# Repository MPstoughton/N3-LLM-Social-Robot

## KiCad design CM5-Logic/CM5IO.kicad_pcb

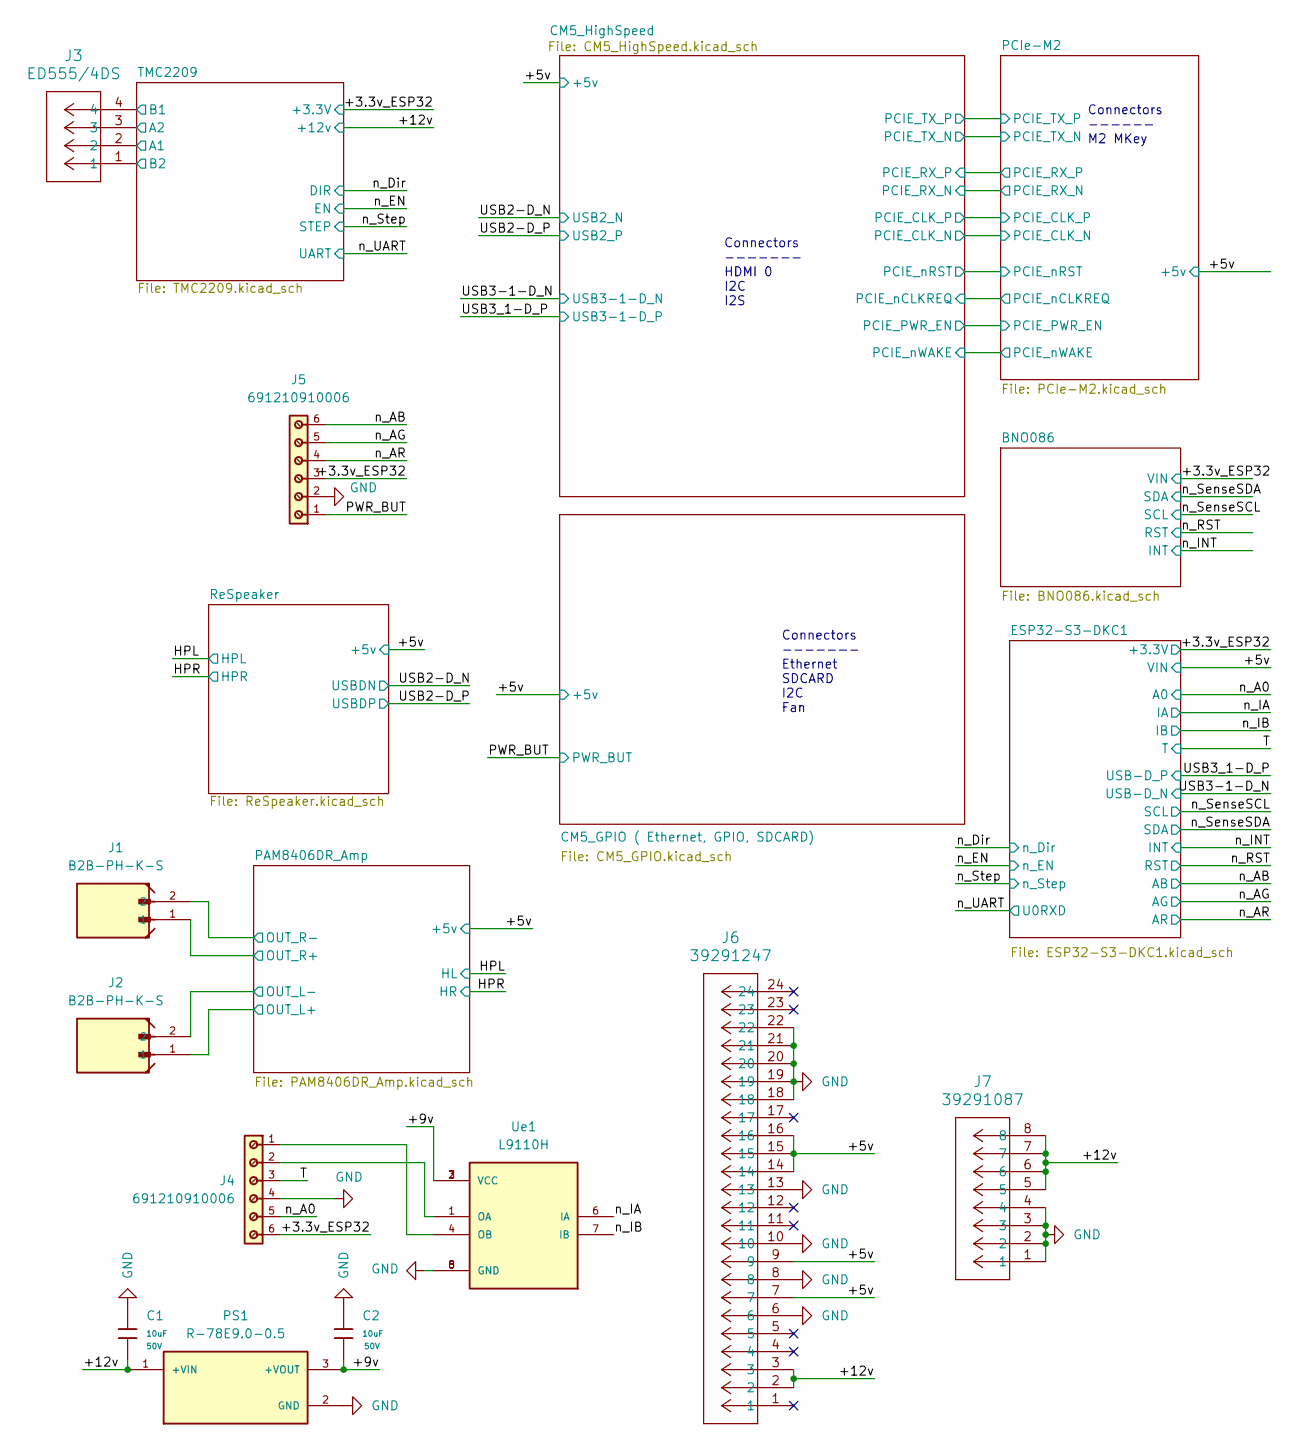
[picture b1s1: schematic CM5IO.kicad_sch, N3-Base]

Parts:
C1, C2: 10uF; C_1206; Voltage Rated 50V; Tolerance ±10%; Part CL31A106KBHNNNE; LCSC C13585
J1, J2: B2B-PH-K-S; JST_B2B-PH-K-S
J3: ED555/4DS; CONN4_ED555&slash_4DS_SHT
J4, J5: 691210910006
J6: 39291247; CONN_SD-5569-002_24_MOL
J7: 39291087; CONN_SD-5569-002_08_MOL
PS1: R-78E9.0-0.5; CONV_R-78E9.0-0.5; PARTREV 4
Ue1: L9110H; SOIC127P599X172-8N; PARTREV NA

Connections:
/+3.3v_ESP32: J4.6, J5.3; also elsewhere on the board
/+5v: J6.7, J6.9, J6.14, J6.15, J6.16; also elsewhere on the board
/+9v: C2.1, PS1.3 (+VOUT), Ue1.2 (VCC), Ue1.3 (VCC)
/+12v: C1.1, J6.2, J6.3, J7.5, J7.6, J7.7, J7.8, PS1.1 (+VIN); also elsewhere on the board
/PAM8406DR_Amp/OUT_L+: J2.1; also elsewhere on the board
/PAM8406DR_Amp/OUT_L-: J2.2; also elsewhere on the board
/PAM8406DR_Amp/OUT_R+: J1.1; also elsewhere on the board
/PAM8406DR_Amp/OUT_R-: J1.2; also elsewhere on the board
/PWR_BUT: J5.1; also elsewhere on the board
/T: J4.3; also elsewhere on the board
/TMC2209/A1: J3.2; also elsewhere on the board
/TMC2209/A2: J3.3; also elsewhere on the board
/TMC2209/B1: J3.4; also elsewhere on the board
/TMC2209/B2: J3.1; also elsewhere on the board
/n_A0: J4.5; also elsewhere on the board
/n_AB: J5.6; also elsewhere on the board
/n_AG: J5.5; also elsewhere on the board
/n_AR: J5.4; also elsewhere on the board
/n_IA: Ue1.6 (IA); also elsewhere on the board
/n_IB: Ue1.7 (IB); also elsewhere on the board
GND: C1.2, C2.2, J4.4, J5.2, J6.6, J6.8, J6.10, J6.13, J6.18, J6.19, J6.20, J6.21, J6.22, J7.1, J7.2, J7.3, J7.4, PS1.2 (GND), Ue1.5 (GND), Ue1.8 (GND); also elsewhere on the board
unnamed: J4.2, Ue1.1 (OA)
unnamed: J4.1, Ue1.4 (OB)

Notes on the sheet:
Connectors ------- Ethernet SDCARD I2C Fan
Connectors ------ M2 MKey
Connectors ------- HDMI 0 I2C I2S

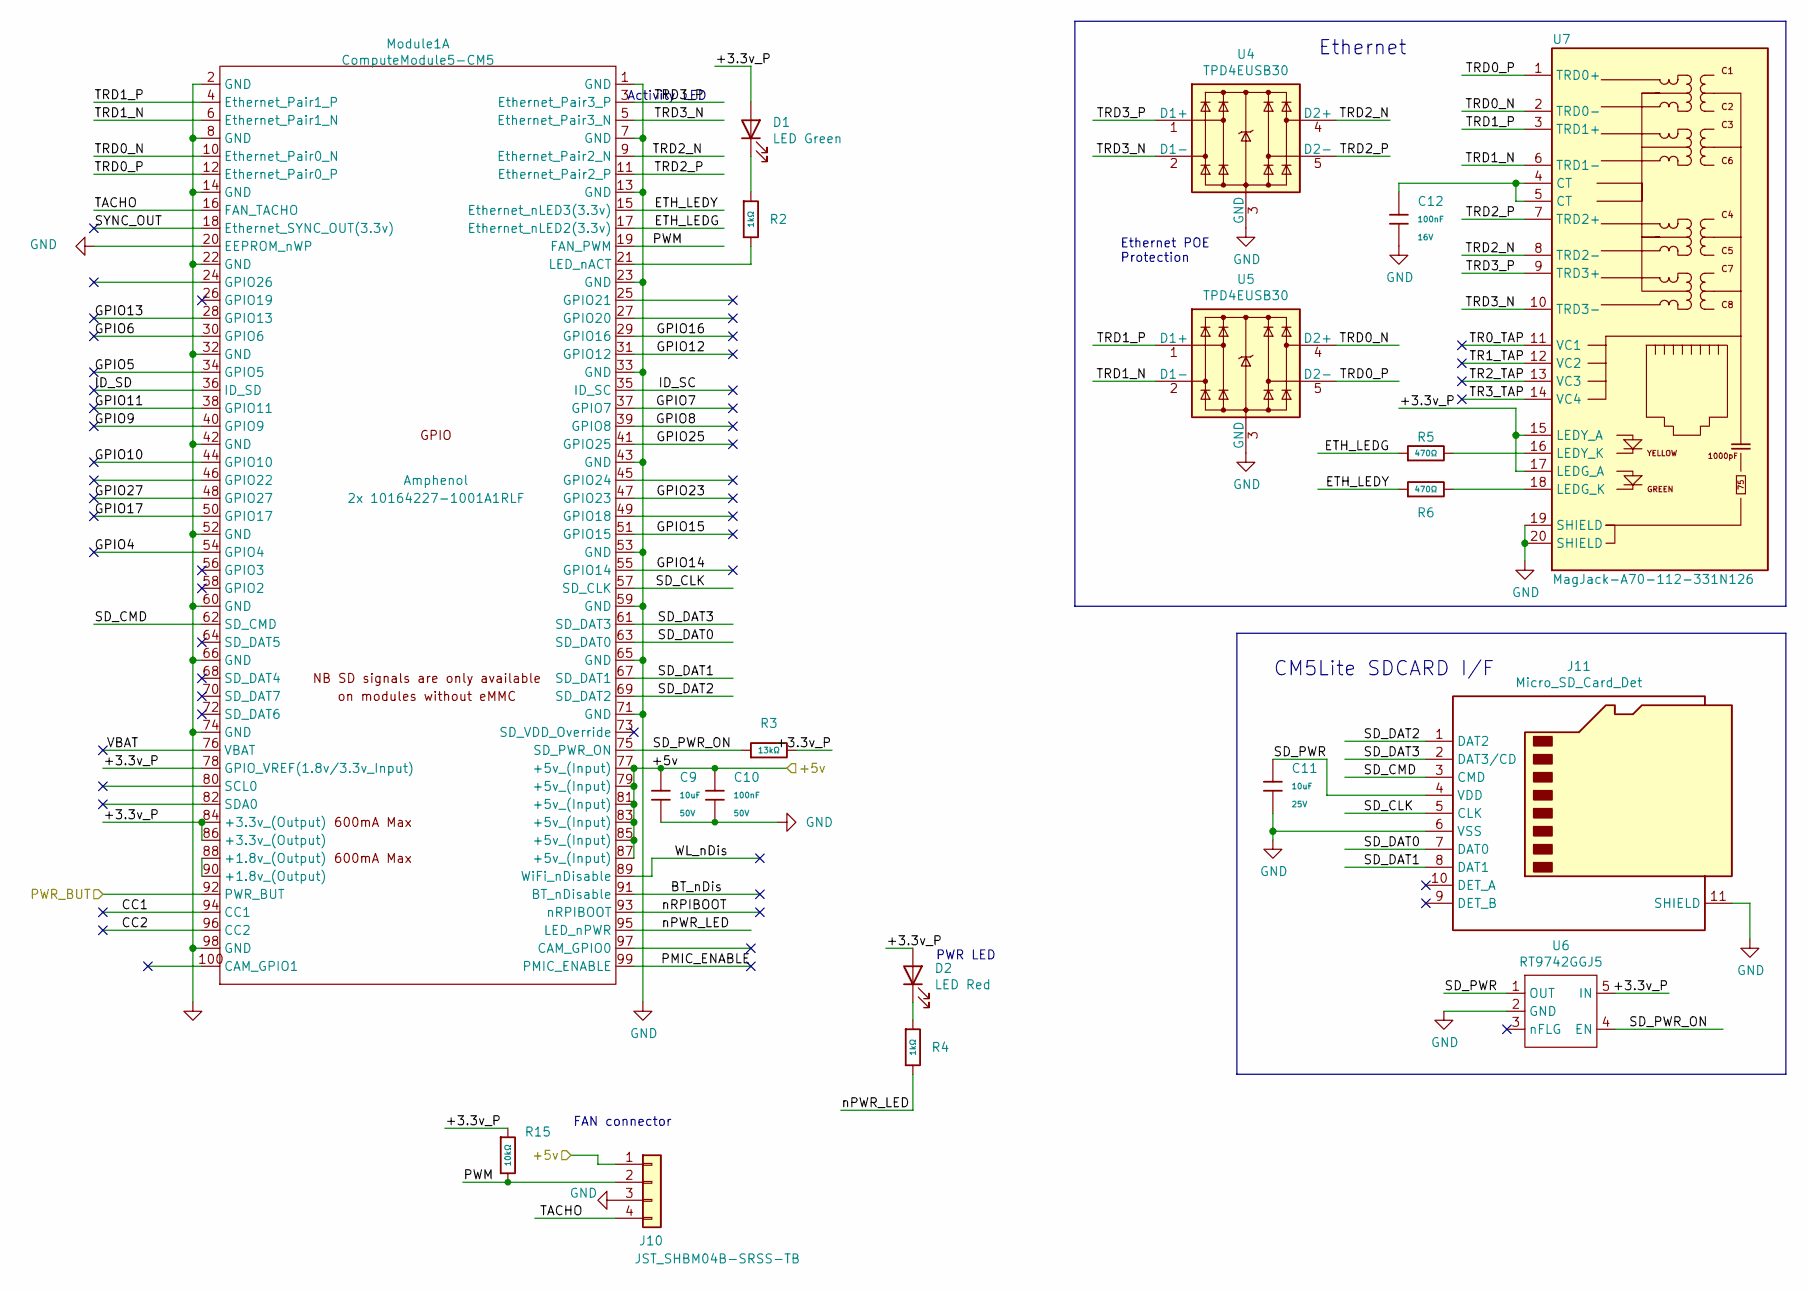
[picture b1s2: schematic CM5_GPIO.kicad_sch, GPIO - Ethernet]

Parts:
C9: 10uF; C_1206; Voltage Rated 50V; Tolerance ±10%; Part CL31A106KBHNNNE; LCSC C13585
C10: 100nF; C_0603; Voltage Rated 50V; Tolerance ±10%; Part CC0603KRX7R9BB104; LCSC C14663
C11: 10uF; C_0805; Voltage Rated 25V; Tolerance ±10%; Part CL21A106KAYNNNE; LCSC C15850
C12: 100nF; C_0402; Voltage Rated 16V; Tolerance ±10%; Part CL05B104KO5NNNC; LCSC C1525
D1: LED Green; LED_0603_1608Metric; Part Description Green 572nm LED Indication - Discrete 2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
D2: LED Red; LED_0603_1608Metric; Part Description Red 620nm LED Indication - Discrete 2.2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
J10: JST_SHBM04B-SRSS-TB; JST_SH_BM04B-SRSS-TB_1x04-1MP_P1.00mm_Vertical; Part Description 4 pin vertical 1mm pitch connector
J11: Micro_SD_Card_Det; SDCARD_MOLEX_503398-1892; Part Description 9 (8 + 1) Position Card Connector micro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
Module1: ComputeModule5-CM5; Raspberry-Pi-5-Compute-Module; Part Description 100 Position Connector Receptacle, Cent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
R2, R4: 1kΩ; R_0402; Overload Voltage (Max) 50V; Tolerance ±1%; Part 0402WGF1001TCE; LCSC C11702
R3: 13kΩ; R_0805; Overload Voltage (Max) 150V; Tolerance ±1%; Part 0805W8F1302T5E; LCSC C17455
R5, R6: 470Ω; R_0402; Overload Voltage (Max) 50V; Tolerance ±1%; Part 0402WGF4700TCE; LCSC C25117
R15: 10kΩ; R_0402; Overload Voltage (Max) 50V; Tolerance ±1%; Part 0402WGF1002TCE; LCSC C25744
U4, U5: TPD4EUSB30; USON-10_2.5x1.0mm_P0.5mm; Part Description Quad TVS diode for high speed signals (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
U6: RT9742GGJ5; SOT-23-5; Part Description Power Switch/Driver 1:1 N-Channel 1A TS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
U7: MagJack-A70-112-331N126; TRJG0926HENL; Part Description Gigabit Ethernet Magjack

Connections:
/+5v: C9.1, C10.1, J10.1, Module1.77 (+5v_(Input)), Module1.79 (+5v_(Input)), Module1.81 (+5v_(Input)), Module1.83 (+5v_(Input)), Module1.85 (+5v_(Input)), Module1.87 (+5v_(Input)); also elsewhere on the board
/CM5_GPIO ( Ethernet, GPIO, SDCARD)/+3.3v_P: D1.2 (A), D2.2 (A), Module1.78 (GPIO_VREF(1.8v/3.3v_Input)), Module1.84 (+3.3v_(Output)), Module1.86 (+3.3v_(Output)), R3.2, R15.1, U6.5 (IN), U7.15 (LEDY_A), U7.17 (LEDG_A)
/CM5_GPIO ( Ethernet, GPIO, SDCARD)/BT_nDis: Module1.91 (BT_nDisable)
/CM5_GPIO ( Ethernet, GPIO, SDCARD)/CC1: Module1.94 (CC1)
/CM5_GPIO ( Ethernet, GPIO, SDCARD)/CC2: Module1.96 (CC2)
/CM5_GPIO ( Ethernet, GPIO, SDCARD)/ETH_LEDG: Module1.17 (Ethernet_nLED2(3.3v)), R5.1
/CM5_GPIO ( Ethernet, GPIO, SDCARD)/ETH_LEDY: Module1.15 (Ethernet_nLED3(3.3v)), R6.1
/CM5_GPIO ( Ethernet, GPIO, SDCARD)/GPIO4: Module1.54 (GPIO4)
/CM5_GPIO ( Ethernet, GPIO, SDCARD)/GPIO5: Module1.34 (GPIO5)
/CM5_GPIO ( Ethernet, GPIO, SDCARD)/GPIO6: Module1.30 (GPIO6)
/CM5_GPIO ( Ethernet, GPIO, SDCARD)/GPIO7: Module1.37 (GPIO7)
/CM5_GPIO ( Ethernet, GPIO, SDCARD)/GPIO8: Module1.39 (GPIO8)
/CM5_GPIO ( Ethernet, GPIO, SDCARD)/GPIO9: Module1.40 (GPIO9)
/CM5_GPIO ( Ethernet, GPIO, SDCARD)/GPIO10: Module1.44 (GPIO10)
/CM5_GPIO ( Ethernet, GPIO, SDCARD)/GPIO11: Module1.38 (GPIO11)
/CM5_GPIO ( Ethernet, GPIO, SDCARD)/GPIO12: Module1.31 (GPIO12)
/CM5_GPIO ( Ethernet, GPIO, SDCARD)/GPIO13: Module1.28 (GPIO13)
/CM5_GPIO ( Ethernet, GPIO, SDCARD)/GPIO14: Module1.55 (GPIO14)
/CM5_GPIO ( Ethernet, GPIO, SDCARD)/GPIO15: Module1.51 (GPIO15)
/CM5_GPIO ( Ethernet, GPIO, SDCARD)/GPIO16: Module1.29 (GPIO16)
/CM5_GPIO ( Ethernet, GPIO, SDCARD)/GPIO17: Module1.50 (GPIO17)
/CM5_GPIO ( Ethernet, GPIO, SDCARD)/GPIO23: Module1.47 (GPIO23)
/CM5_GPIO ( Ethernet, GPIO, SDCARD)/GPIO25: Module1.41 (GPIO25)
/CM5_GPIO ( Ethernet, GPIO, SDCARD)/GPIO27: Module1.48 (GPIO27)
/CM5_GPIO ( Ethernet, GPIO, SDCARD)/ID_SC: Module1.35 (ID_SC)
/CM5_GPIO ( Ethernet, GPIO, SDCARD)/ID_SD: Module1.36 (ID_SD)
/CM5_GPIO ( Ethernet, GPIO, SDCARD)/PMIC_ENABLE: Module1.99 (PMIC_ENABLE)
/CM5_GPIO ( Ethernet, GPIO, SDCARD)/PWM: J10.2, Module1.19 (FAN_PWM), R15.2
/CM5_GPIO ( Ethernet, GPIO, SDCARD)/SD_CLK: J11.5 (CLK), Module1.57 (SD_CLK)
/CM5_GPIO ( Ethernet, GPIO, SDCARD)/SD_CMD: J11.3 (CMD), Module1.62 (SD_CMD)
/CM5_GPIO ( Ethernet, GPIO, SDCARD)/SD_DAT0: J11.7 (DAT0), Module1.63 (SD_DAT0)
/CM5_GPIO ( Ethernet, GPIO, SDCARD)/SD_DAT1: J11.8 (DAT1), Module1.67 (SD_DAT1)
/CM5_GPIO ( Ethernet, GPIO, SDCARD)/SD_DAT2: J11.1 (DAT2), Module1.69 (SD_DAT2)
/CM5_GPIO ( Ethernet, GPIO, SDCARD)/SD_DAT3: J11.2 (DAT3/CD), Module1.61 (SD_DAT3)
/CM5_GPIO ( Ethernet, GPIO, SDCARD)/SD_PWR: C11.1, J11.4 (VDD), U6.1 (OUT)
/CM5_GPIO ( Ethernet, GPIO, SDCARD)/SD_PWR_ON: Module1.75 (SD_PWR_ON), R3.1, U6.4 (EN)
/CM5_GPIO ( Ethernet, GPIO, SDCARD)/SYNC_OUT: Module1.18 (Ethernet_SYNC_OUT(3.3v))
/CM5_GPIO ( Ethernet, GPIO, SDCARD)/TACHO: J10.4, Module1.16 (FAN_TACHO)
/CM5_GPIO ( Ethernet, GPIO, SDCARD)/TR0_TAP: U7.11 (VC1)
/CM5_GPIO ( Ethernet, GPIO, SDCARD)/TR1_TAP: U7.12 (VC2)
/CM5_GPIO ( Ethernet, GPIO, SDCARD)/TR2_TAP: U7.13 (VC3)
/CM5_GPIO ( Ethernet, GPIO, SDCARD)/TR3_TAP: U7.14 (VC4)
/CM5_GPIO ( Ethernet, GPIO, SDCARD)/TRD0_N: Module1.10 (Ethernet_Pair0_N), U5.4 (D2+), U5.7, U7.2 (TRD0-)
/CM5_GPIO ( Ethernet, GPIO, SDCARD)/TRD0_P: Module1.12 (Ethernet_Pair0_P), U5.5 (D2-), U5.6, U7.1 (TRD0+)
/CM5_GPIO ( Ethernet, GPIO, SDCARD)/TRD1_N: Module1.6 (Ethernet_Pair1_N), U5.2 (D1-), U5.9, U7.6 (TRD1-)
/CM5_GPIO ( Ethernet, GPIO, SDCARD)/TRD1_P: Module1.4 (Ethernet_Pair1_P), U5.1 (D1+), U5.10, U7.3 (TRD1+)
/CM5_GPIO ( Ethernet, GPIO, SDCARD)/TRD2_N: Module1.9 (Ethernet_Pair2_N), U4.4 (D2+), U4.7, U7.8 (TRD2-)
/CM5_GPIO ( Ethernet, GPIO, SDCARD)/TRD2_P: Module1.11 (Ethernet_Pair2_P), U4.5 (D2-), U4.6, U7.7 (TRD2+)
/CM5_GPIO ( Ethernet, GPIO, SDCARD)/TRD3_N: Module1.5 (Ethernet_Pair3_N), U4.2 (D1-), U4.9, U7.10 (TRD3-)
/CM5_GPIO ( Ethernet, GPIO, SDCARD)/TRD3_P: Module1.3 (Ethernet_Pair3_P), U4.1 (D1+), U4.10, U7.9 (TRD3+)
/CM5_GPIO ( Ethernet, GPIO, SDCARD)/VBAT: Module1.76 (VBAT)
/CM5_GPIO ( Ethernet, GPIO, SDCARD)/WL_nDis: Module1.89 (WiFi_nDisable)
/CM5_GPIO ( Ethernet, GPIO, SDCARD)/nPWR_LED: Module1.95 (LED_nPWR), R4.2
/CM5_GPIO ( Ethernet, GPIO, SDCARD)/nRPIBOOT: Module1.93 (nRPIBOOT)
/PWR_BUT: Module1.92 (PWR_BUT); also elsewhere on the board
GND: C9.2, C10.2, C11.2, C12.2, J10.3, J11.6 (VSS), J11.11 (SHIELD), Module1.1 (GND), Module1.2 (GND), Module1.7 (GND), Module1.8 (GND), Module1.13 (GND), Module1.14 (GND), Module1.20 (EEPROM_nWP), Module1.22 (GND), Module1.23 (GND), Module1.32 (GND), Module1.33 (GND), Module1.42 (GND), Module1.43 (GND), Module1.52 (GND), Module1.53 (GND), Module1.59 (GND), Module1.60 (GND), Module1.65 (GND), Module1.66 (GND), Module1.71 (GND), Module1.74 (GND), Module1.98 (GND), U4.3 (GND), U4.8 (GND), U5.3 (GND), U5.8 (GND), U6.2 (GND), U7.19 (SHIELD), U7.20 (SHIELD); also elsewhere on the board
unnamed: C12.1, U7.4 (CT), U7.5 (CT)
unnamed: D1.1 (K), R2.1
unnamed: D2.1 (K), R4.1
unnamed: Module1.88 (+1.8v_(Output)), Module1.90 (+1.8v_(Output))
unnamed: Module1.21 (LED_nACT), R2.2
unnamed: R6.2, U7.18 (LEDG_K)
unnamed: R5.2, U7.16 (LEDY_K)

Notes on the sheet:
Activity LED
FAN connector
Ethernet POE Protection
PWR LED
Ethernet
CM5Lite SDCARD I/F

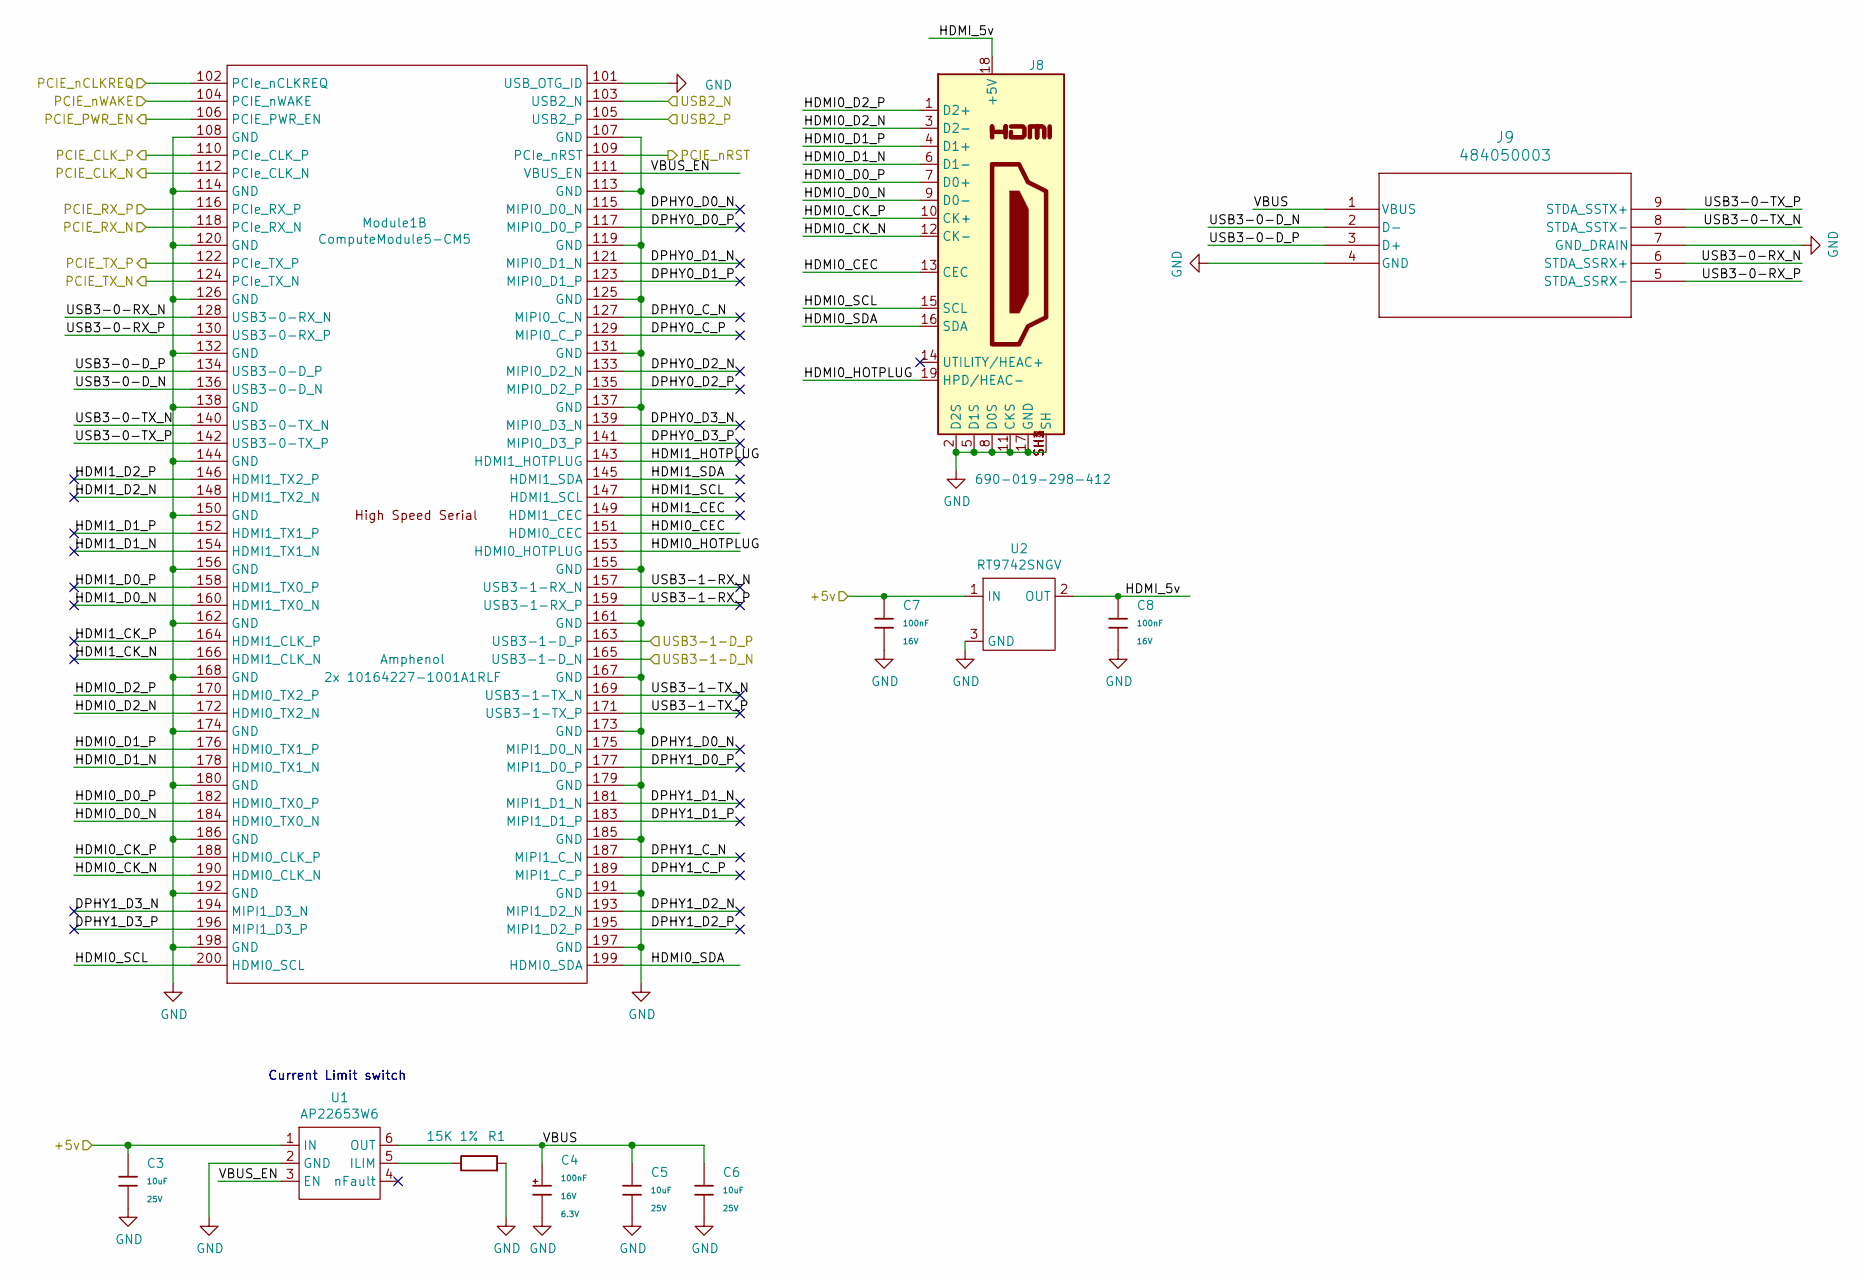
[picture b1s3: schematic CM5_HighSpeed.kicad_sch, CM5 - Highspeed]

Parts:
C3, C5, C6: 10uF; C_0805; Voltage Rated 25V; Tolerance ±10%; Part CL21A106KAYNNNE; LCSC C15850
C4: 100nF; C_CASE-B-3528-21(mm); Voltage Rated 16V; Tolerance ±10%; Part TAJB107K006RNJ; LCSC C16133
C7, C8: 100nF; C_0402; Voltage Rated 16V; Tolerance ±10%; Part CL05B104KO5NNNC; LCSC C1525
J8: 690-019-298-412; EDAC 690-019-298-412; Part Description HDMI Connector, Right Angle, 19 Contact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
J9: 484050003; 484050003_MOL
Module1: ComputeModule5-CM5; Raspberry-Pi-5-Compute-Module; Part Description 100 Position Connector Receptacle, Cent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
R1: 15K 1%; R_0402_1005Metric; Part Description Resistor 15K M1005 1% 63mW
U1: AP22653W6; SOT-23-6; Part Description Power Switch/Driver 1:1 P-Channel 2.1A 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
U2: RT9742SNGV; TSOT-23_HandSoldering; Part Description Power Switch/Driver 1:1 N-Channel 500mA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

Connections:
/+5v: C3.1, C7.1, U1.1 (IN), U2.1 (IN); also elsewhere on the board
/CM5_HighSpeed/DPHY0_C_N: Module1.127 (MIPI0_C_N)
/CM5_HighSpeed/DPHY0_C_P: Module1.129 (MIPI0_C_P)
/CM5_HighSpeed/DPHY0_D0_N: Module1.115 (MIPI0_D0_N)
/CM5_HighSpeed/DPHY0_D0_P: Module1.117 (MIPI0_D0_P)
/CM5_HighSpeed/DPHY0_D1_N: Module1.121 (MIPI0_D1_N)
/CM5_HighSpeed/DPHY0_D1_P: Module1.123 (MIPI0_D1_P)
/CM5_HighSpeed/DPHY0_D2_N: Module1.133 (MIPI0_D2_N)
/CM5_HighSpeed/DPHY0_D2_P: Module1.135 (MIPI0_D2_P)
/CM5_HighSpeed/DPHY0_D3_N: Module1.139 (MIPI0_D3_N)
/CM5_HighSpeed/DPHY0_D3_P: Module1.141 (MIPI0_D3_P)
/CM5_HighSpeed/DPHY1_C_N: Module1.187 (MIPI1_C_N)
/CM5_HighSpeed/DPHY1_C_P: Module1.189 (MIPI1_C_P)
/CM5_HighSpeed/DPHY1_D0_N: Module1.175 (MIPI1_D0_N)
/CM5_HighSpeed/DPHY1_D0_P: Module1.177 (MIPI1_D0_P)
/CM5_HighSpeed/DPHY1_D1_N: Module1.181 (MIPI1_D1_N)
/CM5_HighSpeed/DPHY1_D1_P: Module1.183 (MIPI1_D1_P)
/CM5_HighSpeed/DPHY1_D2_N: Module1.193 (MIPI1_D2_N)
/CM5_HighSpeed/DPHY1_D2_P: Module1.195 (MIPI1_D2_P)
/CM5_HighSpeed/DPHY1_D3_N: Module1.194 (MIPI1_D3_N)
/CM5_HighSpeed/DPHY1_D3_P: Module1.196 (MIPI1_D3_P)
/CM5_HighSpeed/HDMI0_CEC: J8.13 (CEC), Module1.151 (HDMI0_CEC)
/CM5_HighSpeed/HDMI0_CK_N: J8.12 (CK-), Module1.190 (HDMI0_CLK_N)
/CM5_HighSpeed/HDMI0_CK_P: J8.10 (CK+), Module1.188 (HDMI0_CLK_P)
/CM5_HighSpeed/HDMI0_D0_N: J8.9 (D0-), Module1.184 (HDMI0_TX0_N)
/CM5_HighSpeed/HDMI0_D0_P: J8.7 (D0+), Module1.182 (HDMI0_TX0_P)
/CM5_HighSpeed/HDMI0_D1_N: J8.6 (D1-), Module1.178 (HDMI0_TX1_N)
/CM5_HighSpeed/HDMI0_D1_P: J8.4 (D1+), Module1.176 (HDMI0_TX1_P)
/CM5_HighSpeed/HDMI0_D2_N: J8.3 (D2-), Module1.172 (HDMI0_TX2_N)
/CM5_HighSpeed/HDMI0_D2_P: J8.1 (D2+), Module1.170 (HDMI0_TX2_P)
/CM5_HighSpeed/HDMI0_HOTPLUG: J8.19 (HPD/HEAC-), Module1.153 (HDMI0_HOTPLUG)
/CM5_HighSpeed/HDMI0_SCL: J8.15 (SCL), Module1.200 (HDMI0_SCL)
/CM5_HighSpeed/HDMI0_SDA: J8.16 (SDA), Module1.199 (HDMI0_SDA)
/CM5_HighSpeed/HDMI1_CEC: Module1.149 (HDMI1_CEC)
/CM5_HighSpeed/HDMI1_CK_N: Module1.166 (HDMI1_CLK_N)
/CM5_HighSpeed/HDMI1_CK_P: Module1.164 (HDMI1_CLK_P)
/CM5_HighSpeed/HDMI1_D0_N: Module1.160 (HDMI1_TX0_N)
/CM5_HighSpeed/HDMI1_D0_P: Module1.158 (HDMI1_TX0_P)
/CM5_HighSpeed/HDMI1_D1_N: Module1.154 (HDMI1_TX1_N)
/CM5_HighSpeed/HDMI1_D1_P: Module1.152 (HDMI1_TX1_P)
/CM5_HighSpeed/HDMI1_D2_N: Module1.148 (HDMI1_TX2_N)
/CM5_HighSpeed/HDMI1_D2_P: Module1.146 (HDMI1_TX2_P)
/CM5_HighSpeed/HDMI1_HOTPLUG: Module1.143 (HDMI1_HOTPLUG)
/CM5_HighSpeed/HDMI1_SCL: Module1.147 (HDMI1_SCL)
/CM5_HighSpeed/HDMI1_SDA: Module1.145 (HDMI1_SDA)
/CM5_HighSpeed/HDMI_5v: C8.1, J8.18 (+5V), U2.2 (OUT)
/CM5_HighSpeed/PCIE_CLK_N: Module1.112 (PCIe_CLK_N); also elsewhere on the board
/CM5_HighSpeed/PCIE_CLK_P: Module1.110 (PCIe_CLK_P); also elsewhere on the board
/CM5_HighSpeed/PCIE_PWR_EN: Module1.106 (PCIE_PWR_EN); also elsewhere on the board
/CM5_HighSpeed/PCIE_RX_N: Module1.118 (PCIe_RX_N); also elsewhere on the board
/CM5_HighSpeed/PCIE_RX_P: Module1.116 (PCIe_RX_P); also elsewhere on the board
/CM5_HighSpeed/PCIE_TX_N: Module1.124 (PCIe_TX_N); also elsewhere on the board
/CM5_HighSpeed/PCIE_TX_P: Module1.122 (PCIe_TX_P); also elsewhere on the board
/CM5_HighSpeed/PCIE_nCLKREQ: Module1.102 (PCIe_nCLKREQ); also elsewhere on the board
/CM5_HighSpeed/PCIE_nRST: Module1.109 (PCIe_nRST); also elsewhere on the board
/CM5_HighSpeed/PCIE_nWAKE: Module1.104 (PCIE_nWAKE); also elsewhere on the board
/CM5_HighSpeed/USB3-0-D_N: J9.2 (D-), Module1.136 (USB3-0-D_N)
/CM5_HighSpeed/USB3-0-D_P: J9.3 (D+), Module1.134 (USB3-0-D_P)
/CM5_HighSpeed/USB3-0-RX_N: J9.6 (STDA_SSRX+), Module1.128 (USB3-0-RX_N)
/CM5_HighSpeed/USB3-0-RX_P: J9.5 (STDA_SSRX-), Module1.130 (USB3-0-RX_P)
/CM5_HighSpeed/USB3-0-TX_N: J9.8 (STDA_SSTX-), Module1.140 (USB3-0-TX_N)
/CM5_HighSpeed/USB3-0-TX_P: J9.9 (STDA_SSTX+), Module1.142 (USB3-0-TX_P)
/CM5_HighSpeed/USB3-1-RX_N: Module1.157 (USB3-1-RX_N)
/CM5_HighSpeed/USB3-1-RX_P: Module1.159 (USB3-1-RX_P)
/CM5_HighSpeed/USB3-1-TX_N: Module1.169 (USB3-1-TX_N)
/CM5_HighSpeed/USB3-1-TX_P: Module1.171 (USB3-1-TX_P)
/CM5_HighSpeed/VBUS: C4.1, C5.1, C6.1, J9.1 (VBUS), U1.6 (OUT)
/CM5_HighSpeed/VBUS_EN: Module1.111 (VBUS_EN), U1.3 (EN)
/USB2-D_N: Module1.103 (USB2_N); also elsewhere on the board
/USB2-D_P: Module1.105 (USB2_P); also elsewhere on the board
/USB3-1-D_N: Module1.165 (USB3-1-D_N); also elsewhere on the board
/USB3_1-D_P: Module1.163 (USB3-1-D_P); also elsewhere on the board
GND: C3.2, C4.2, C5.2, C6.2, C7.2, C8.2, J8.2 (D2S), J8.5 (D1S), J8.8 (D0S), J8.11 (CKS), J8.17 (GND), J8.SH1 (SH), J8.SH2 (SH), J8.SH3 (SH), J8.SH4 (SH), J9.4 (GND), J9.7 (GND_DRAIN), Module1.101 (USB_OTG_ID), Module1.107 (GND), Module1.108 (GND), Module1.113 (GND), Module1.114 (GND), Module1.119 (GND), Module1.120 (GND), Module1.125 (GND), Module1.126 (GND), Module1.131 (GND), Module1.132 (GND), Module1.137 (GND), Module1.138 (GND), Module1.144 (GND), Module1.150 (GND), Module1.155 (GND), Module1.156 (GND), Module1.161 (GND), Module1.162 (GND), Module1.167 (GND), Module1.168 (GND), Module1.173 (GND), Module1.174 (GND), Module1.179 (GND), Module1.180 (GND), Module1.185 (GND), Module1.186 (GND), Module1.191 (GND), Module1.192 (GND), Module1.197 (GND), Module1.198 (GND), R1.2, U1.2 (GND), U2.3 (GND); also elsewhere on the board
unnamed: R1.1, U1.5 (ILIM)

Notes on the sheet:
Current Limit switch

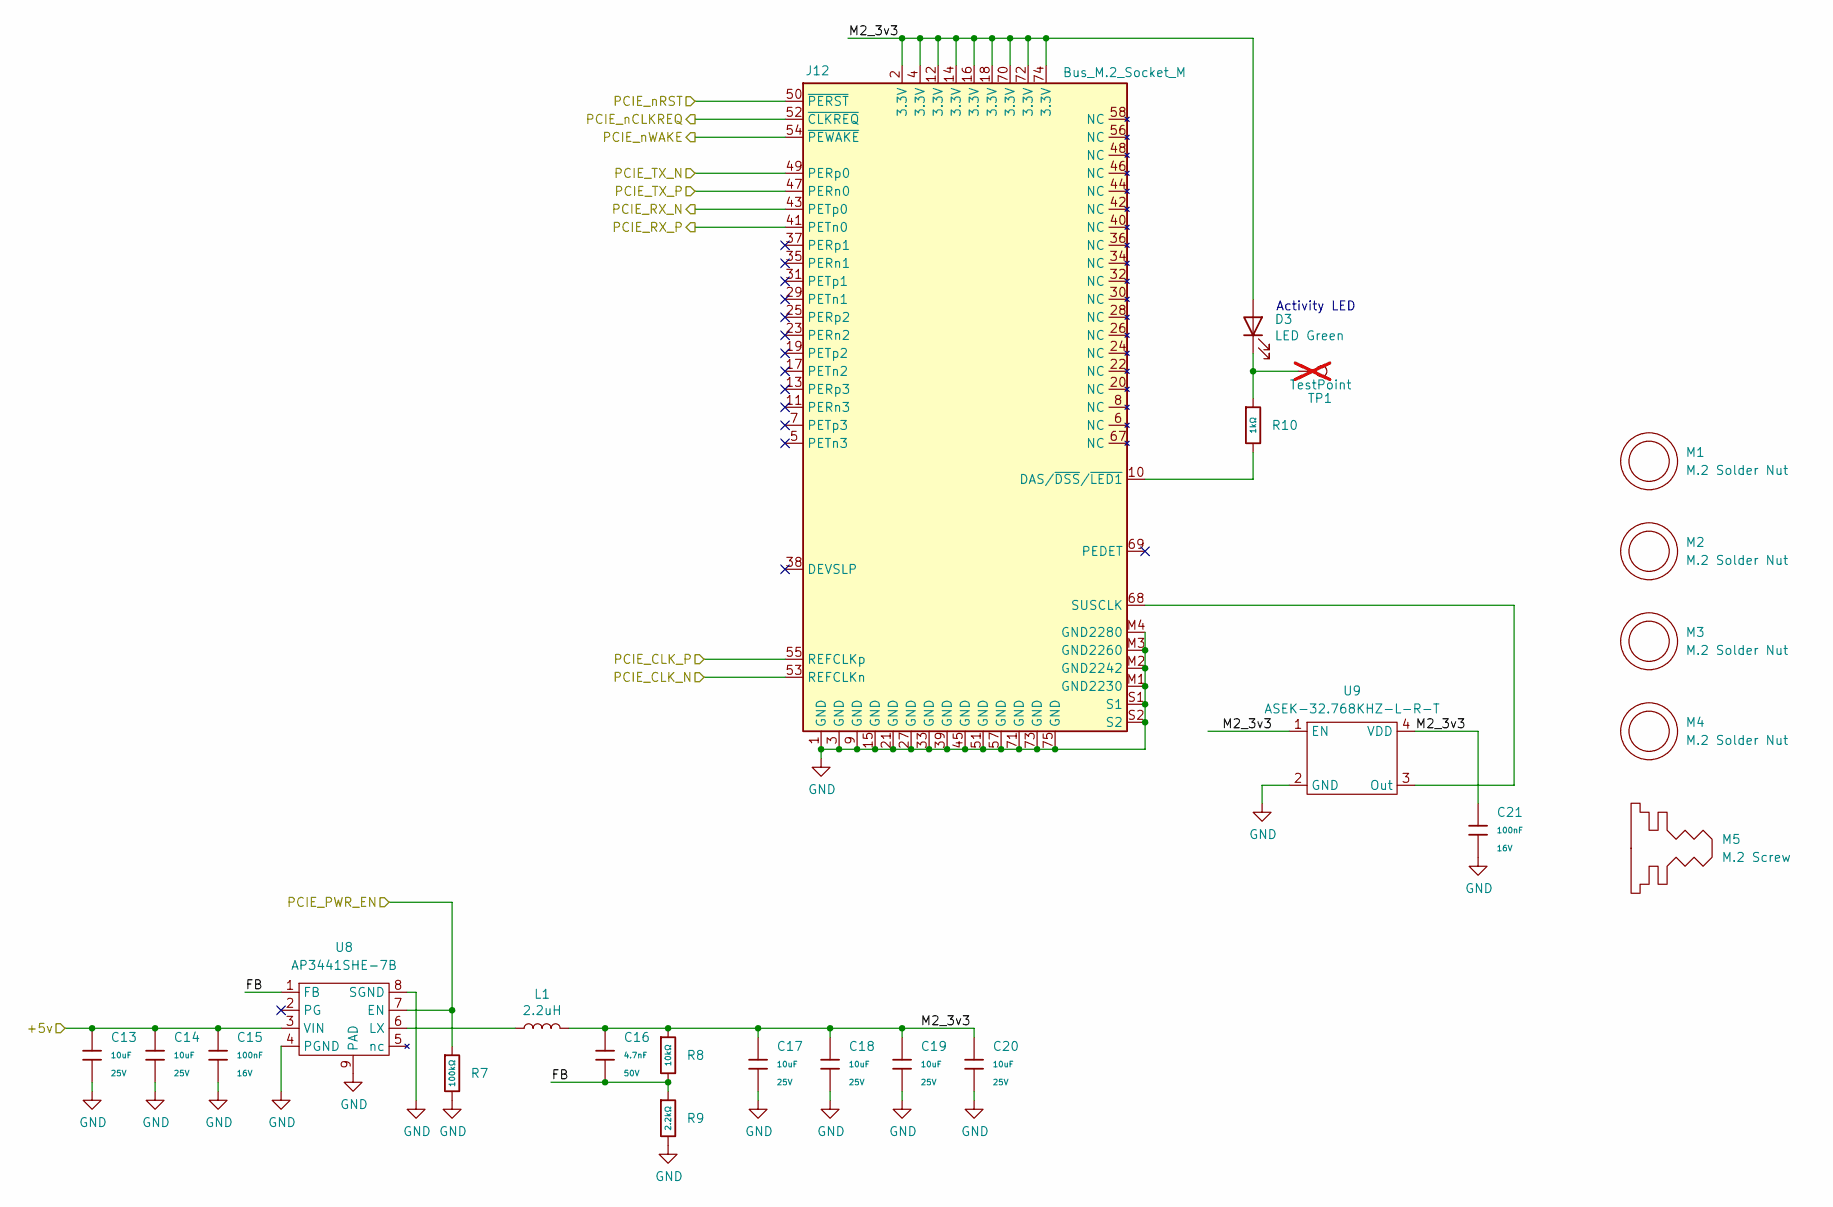
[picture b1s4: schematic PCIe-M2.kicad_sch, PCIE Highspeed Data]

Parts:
C13, C14, C17, C18, C19, C20: 10uF; C_0805; Voltage Rated 25V; Tolerance ±10%; Part CL21A106KAYNNNE; LCSC C15850
C15, C21: 100nF; C_0402; Voltage Rated 16V; Tolerance ±10%; Part CL05B104KO5NNNC; LCSC C1525
C16: 4.7nF; C_0402; Voltage Rated 50V; Tolerance ±10%; Part 0402B472K500NT; LCSC C1538
D3: LED Green; LED_0603_1608Metric; Part Description Green 572nm LED Indication - Discrete 2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
J12: Bus_M.2_Socket_M; M.2 M Key socket; Part Description M.2 M Key connector
L1: 2.2uH; L_Bourns_SRP5030CC; Part Description Inductor, SMT, 2520, 2u2, IRMS=7A, ISAT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
M1, M2, M3, M4: M.2 Solder Nut; Part Description Solder nut for M.2 slot
M5: M.2 Screw; Part Description M.2 Screw
R7: 100kΩ; R_0402; Overload Voltage (Max) 50V; Tolerance ±1%; Part 0402WGF1003TCE; LCSC C25741
R8: 10kΩ; R_0402; Overload Voltage (Max) 50V; Tolerance ±1%; Part 0402WGF1002TCE; LCSC C25744
R9: 2.2kΩ; R_0402; Overload Voltage (Max) 50V; Tolerance ±1%; Part 0402WGF2201TCE; LCSC C25879
R10: 1kΩ; R_0402; Overload Voltage (Max) 50V; Tolerance ±1%; Part 0402WGF1001TCE; LCSC C11702
TP1: TestPoint; TestPoint_Pad_2.0x2.0mm; Part Description Test point; not fitted
U8: AP3441SHE-7B; DFN-8-1EP_2x2mm_P0.5mm_EP1.05x1.75mm; Part Description 3A DC-DC converter
U9: ASEK-32.768KHZ-L-R-T; Crystal_SMD_3225-4Pin_3.2x2.5mm; Part Description 32KHz Xtal oscilator

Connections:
/+5v: C13.1, C14.1, C15.1, U8.3 (VIN); also elsewhere on the board
/CM5_HighSpeed/PCIE_CLK_N: J12.53 (REFCLKn); also elsewhere on the board
/CM5_HighSpeed/PCIE_CLK_P: J12.55 (REFCLKp); also elsewhere on the board
/CM5_HighSpeed/PCIE_PWR_EN: R7.1, U8.7 (EN); also elsewhere on the board
/CM5_HighSpeed/PCIE_RX_N: J12.43 (PETp0); also elsewhere on the board
/CM5_HighSpeed/PCIE_RX_P: J12.41 (PETn0); also elsewhere on the board
/CM5_HighSpeed/PCIE_TX_N: J12.49 (PERp0); also elsewhere on the board
/CM5_HighSpeed/PCIE_TX_P: J12.47 (PERn0); also elsewhere on the board
/CM5_HighSpeed/PCIE_nCLKREQ: J12.52 (~CLKREQ); also elsewhere on the board
/CM5_HighSpeed/PCIE_nRST: J12.50 (~PERST); also elsewhere on the board
/CM5_HighSpeed/PCIE_nWAKE: J12.54 (~PEWAKE); also elsewhere on the board
/PCIe-M2/FB: C16.2, R8.2, R9.1, U8.1 (FB)
/PCIe-M2/M2_3v3: C16.1, C17.1, C18.1, C19.1, C20.1, C21.1, D3.2 (A), J12.2 (3.3V), J12.4 (3.3V), J12.12 (3.3V), J12.14 (3.3V), J12.16 (3.3V), J12.18 (3.3V), J12.70 (3.3V), J12.72 (3.3V), J12.74 (3.3V), L1.2, R8.1, U9.1 (EN), U9.4 (VDD)
GND: C13.2, C14.2, C15.2, C17.2, C18.2, C19.2, C20.2, C21.2, J12.1 (GND), J12.3 (GND), J12.9 (GND), J12.15 (GND), J12.21 (GND), J12.27 (GND), J12.33 (GND), J12.39 (GND), J12.45 (GND), J12.51 (GND), J12.57 (GND), J12.71 (GND), J12.73 (GND), J12.75 (GND), J12.M1 (GND2230), J12.M2 (GND2242), J12.M3 (GND2260), J12.M4 (GND2280), J12.S1, J12.S2, R7.2, R9.2, U8.4 (PGND), U8.8 (SGND), U8.9 (PAD), U9.2 (GND); also elsewhere on the board
unnamed: D3.1 (K), R10.1, TP1.1
unnamed: J12.10 (DAS/~DSS/~LED1), R10.2
unnamed: J12.68 (SUSCLK), U9.3 (Out)
unnamed: L1.1, U8.6 (LX)

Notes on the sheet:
Activity LED

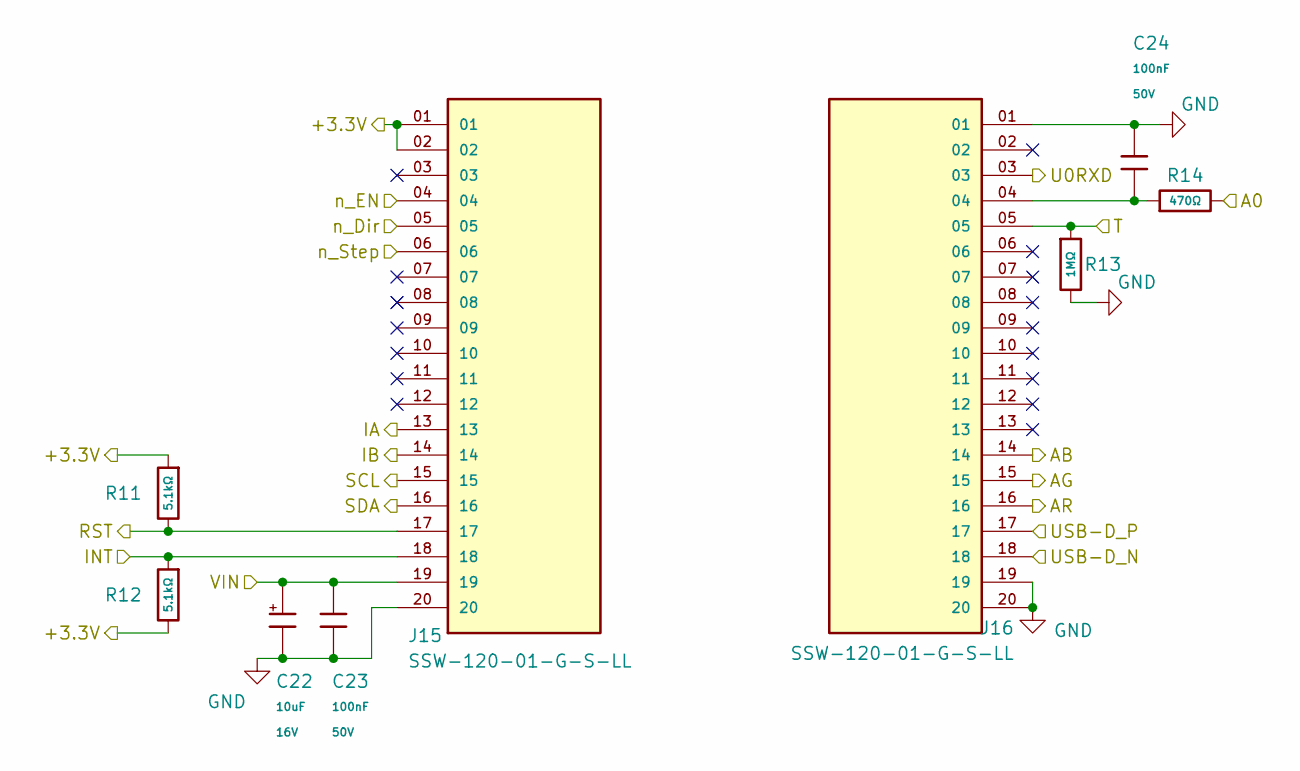
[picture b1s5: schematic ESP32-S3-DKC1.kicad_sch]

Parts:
C22: 10uF; C_CASE-A-3216-18(mm); Tolerance ±10%; Rated Voltage 16V; Part TAJA106K016RNJ; LCSC C7171
C23, C24: 100nF; C_0603; Voltage Rated 50V; Tolerance ±10%; Part CC0603KRX7R9BB104; LCSC C14663
J15, J16: SSW-120-01-G-S-LL; SAMTEC_SSW-120-01-G-S-LL; PARTREV R
R11, R12: 5.1kΩ; R_0603; Overload Voltage (Max) 75V; Tolerance ±1%; Part 0603WAF5101T5E; LCSC C23186
R13: 1MΩ; R_0603; Overload Voltage (Max) 75V; Tolerance ±1%; Part 0603WAF1004T5E; LCSC C22935
R14: 470Ω; R_0603; Overload Voltage (Max) 75V; Tolerance ±1%; Part 0603WAF4700T5E; LCSC C23179

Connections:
/+3.3v_ESP32: J15.01, J15.02, R11.1, R12.2; also elsewhere on the board
/+5v: C22.1, C23.1, J15.19; also elsewhere on the board
/T: J16.05, R13.1; also elsewhere on the board
/USB3-1-D_N: J16.18; also elsewhere on the board
/USB3_1-D_P: J16.17; also elsewhere on the board
/n_A0: R14.2; also elsewhere on the board
/n_AB: J16.14; also elsewhere on the board
/n_AG: J16.15; also elsewhere on the board
/n_AR: J16.16; also elsewhere on the board
/n_Dir: J15.05; also elsewhere on the board
/n_EN: J15.04; also elsewhere on the board
/n_IA: J15.13; also elsewhere on the board
/n_IB: J15.14; also elsewhere on the board
/n_INT: J15.18, R12.1; also elsewhere on the board
/n_RST: J15.17, R11.2; also elsewhere on the board
/n_SenseSCL: J15.15; also elsewhere on the board
/n_SenseSDA: J15.16; also elsewhere on the board
/n_Step: J15.06; also elsewhere on the board
/n_UART: J16.03; also elsewhere on the board
GND: C22.2, C23.2, C24.1, J15.20, J16.01, J16.19, J16.20, R13.2; also elsewhere on the board
unnamed: C24.2, J16.04, R14.1

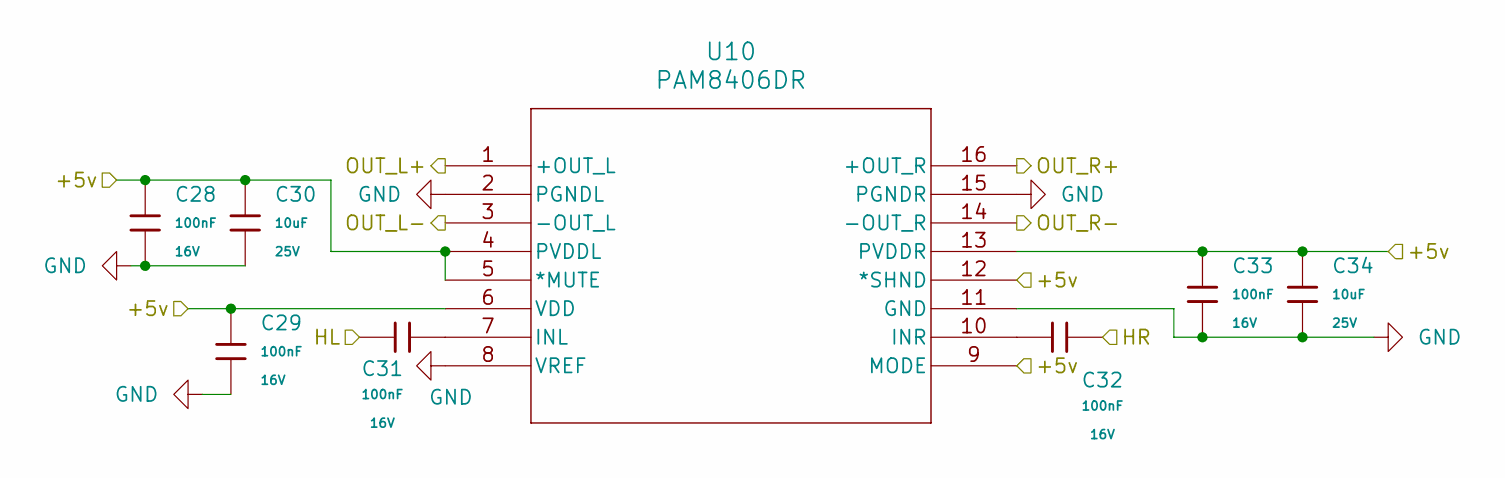
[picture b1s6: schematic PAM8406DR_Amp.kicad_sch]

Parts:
C28, C29, C31, C32, C33: 100nF; C_0402; Voltage Rated 16V; Tolerance ±10%; Part CL05B104KO5NNNC; LCSC C1525
C30, C34: 10uF; C_0805; Voltage Rated 25V; Tolerance ±10%; Part CL21A106KAYNNNE; LCSC C15850
U10: PAM8406DR; SO-16_PAM8406_DIO

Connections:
/+5v: C28.1, C29.1, C30.1, C33.1, C34.1, U10.4 (PVDDL), U10.5 (*MUTE), U10.6 (VDD), U10.9 (MODE), U10.12 (*SHND), U10.13 (PVDDR); also elsewhere on the board
/HPL: C31.2; also elsewhere on the board
/HPR: C32.1; also elsewhere on the board
/PAM8406DR_Amp/OUT_L+: U10.1 (+OUT_L); also elsewhere on the board
/PAM8406DR_Amp/OUT_L-: U10.3 (-OUT_L); also elsewhere on the board
/PAM8406DR_Amp/OUT_R+: U10.16 (+OUT_R); also elsewhere on the board
/PAM8406DR_Amp/OUT_R-: U10.14 (-OUT_R); also elsewhere on the board
GND: C28.2, C29.2, C30.2, C33.2, C34.2, U10.2 (PGNDL), U10.8 (VREF), U10.11 (GND), U10.15 (PGNDR); also elsewhere on the board
unnamed: C31.1, U10.7 (INL)
unnamed: C32.2, U10.10 (INR)
